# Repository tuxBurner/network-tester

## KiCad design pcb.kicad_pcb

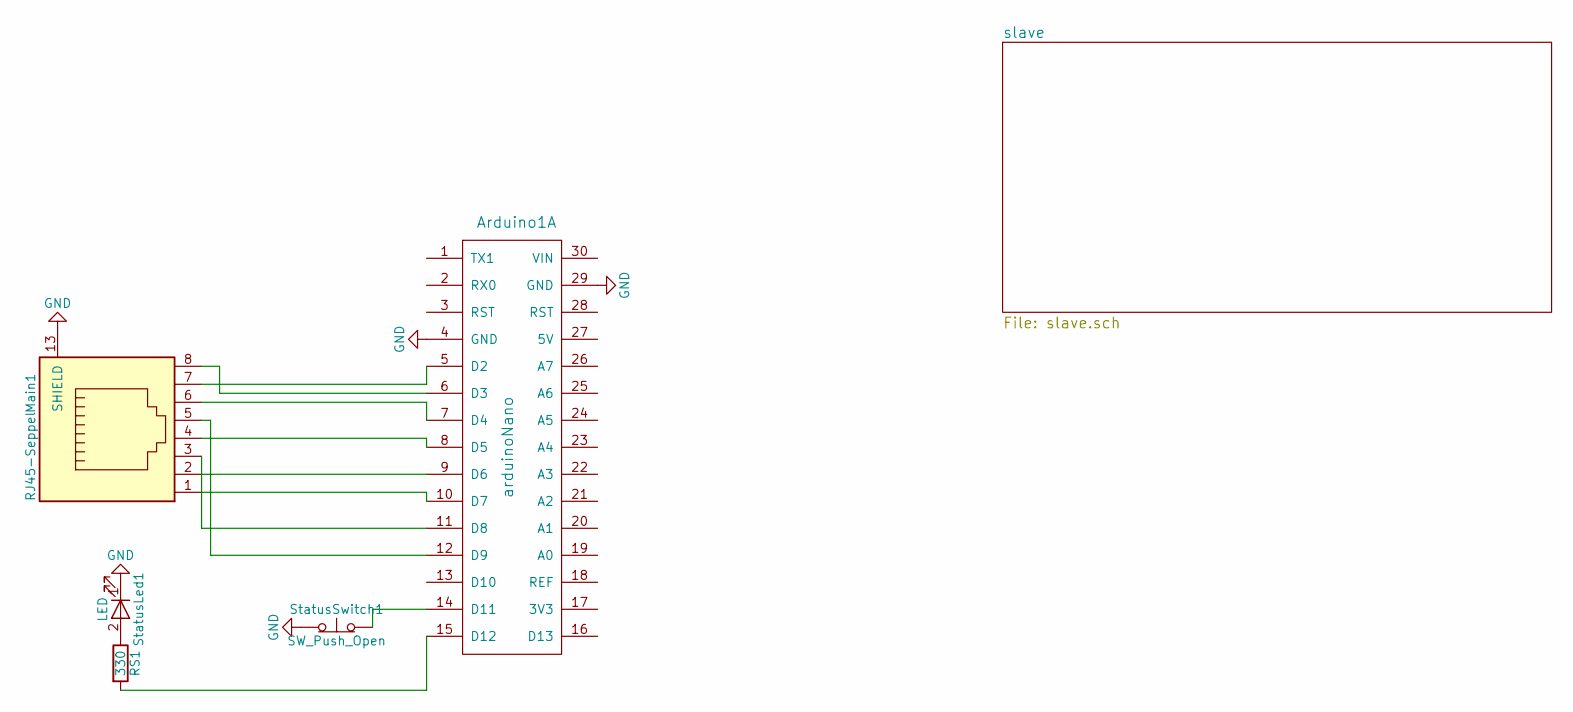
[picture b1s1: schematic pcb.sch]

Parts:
Arduino1: arduinoNano; Arduino_Nano
Main1: RJ45-Seppel; rj45-seppel-small
RS1: 330; R_Axial_DIN0207_L6.3mm_D2.5mm_P10.16mm_Horizontal
StatusLed1: LED; LED_D4.0mm
StatusSwitch1: SW_Push_Open; Pin_Header_Straight_1x02_Pitch2.54mm

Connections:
GND: Arduino1.4 (GND), Arduino1.29 (GND), Main1.13 (SHIELD), StatusLed1.1 (K), StatusSwitch1.1 (A)
unnamed: Arduino1.5 (D2), Main1.7
unnamed: Arduino1.6 (D3), Main1.8
unnamed: Arduino1.7 (D4), Main1.6
unnamed: Arduino1.8 (D5), Main1.4
unnamed: Arduino1.9 (D6), Main1.2
unnamed: Arduino1.10 (D7), Main1.1
unnamed: Arduino1.11 (D8), Main1.3
unnamed: Arduino1.12 (D9), Main1.5
unnamed: Arduino1.14 (D11), StatusSwitch1.2 (B)
unnamed: Arduino1.15 (D12), RS1.2
unnamed: RS1.1, StatusLed1.2 (A)

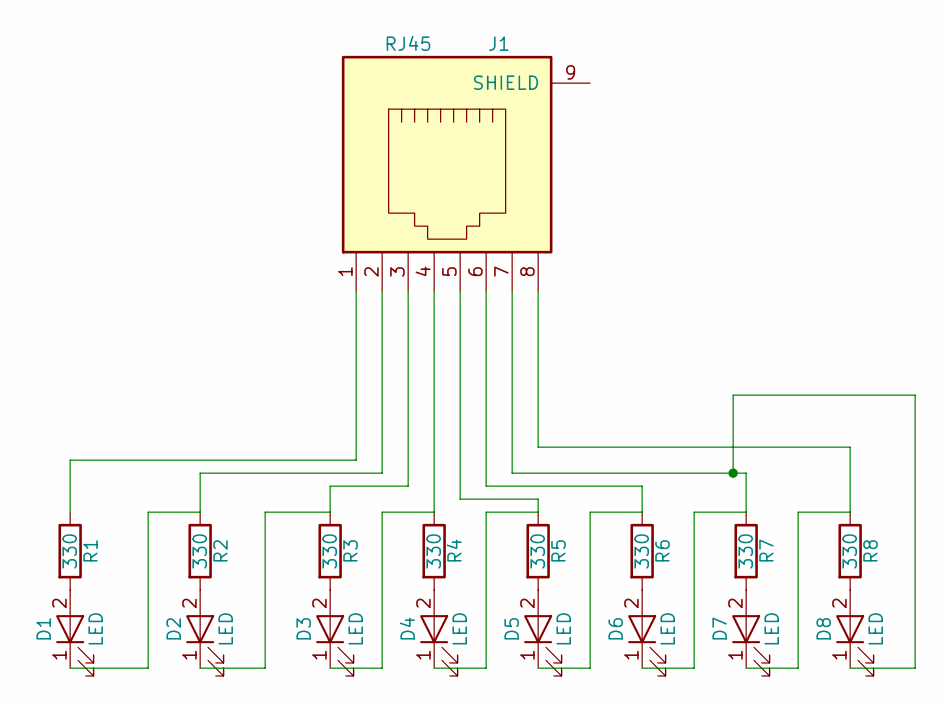
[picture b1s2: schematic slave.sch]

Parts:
D1, D2, D3, D4, D5, D6, D7, D8: LED; LED_D4.0mm
J1: RJ45; rj45-seppel-small
R1, R2, R3, R4, R5, R6, R7, R8: 330; R_Axial_DIN0207_L6.3mm_D2.5mm_P10.16mm_Horizontal

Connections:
unnamed: D1.1 (K), J1.2, R2.1
unnamed: D1.2 (A), R1.2
unnamed: D2.1 (K), J1.3, R3.1
unnamed: D2.2 (A), R2.2
unnamed: D3.1 (K), J1.4, R4.1
unnamed: D3.2 (A), R3.2
unnamed: D4.1 (K), J1.5, R5.1
unnamed: D4.2 (A), R4.2
unnamed: D5.1 (K), J1.6, R6.1
unnamed: D5.2 (A), R5.2
unnamed: D6.1 (K), D8.1 (K), J1.7, R7.1
unnamed: D6.2 (A), R6.2
unnamed: D7.1 (K), J1.8, R8.1
unnamed: D7.2 (A), R7.2
unnamed: D8.2 (A), R8.2
unnamed: J1.1, R1.1

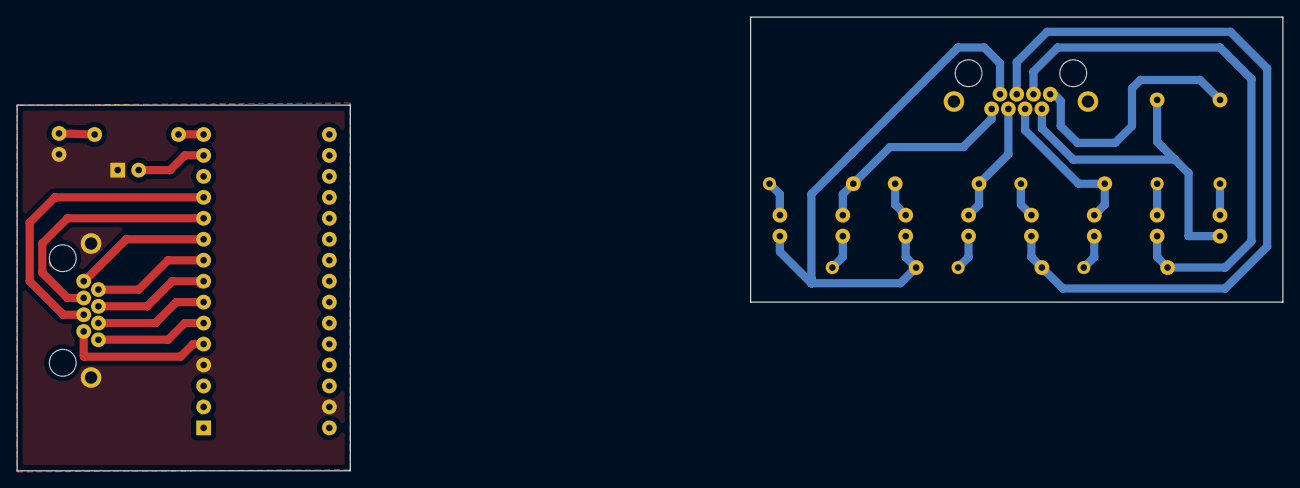
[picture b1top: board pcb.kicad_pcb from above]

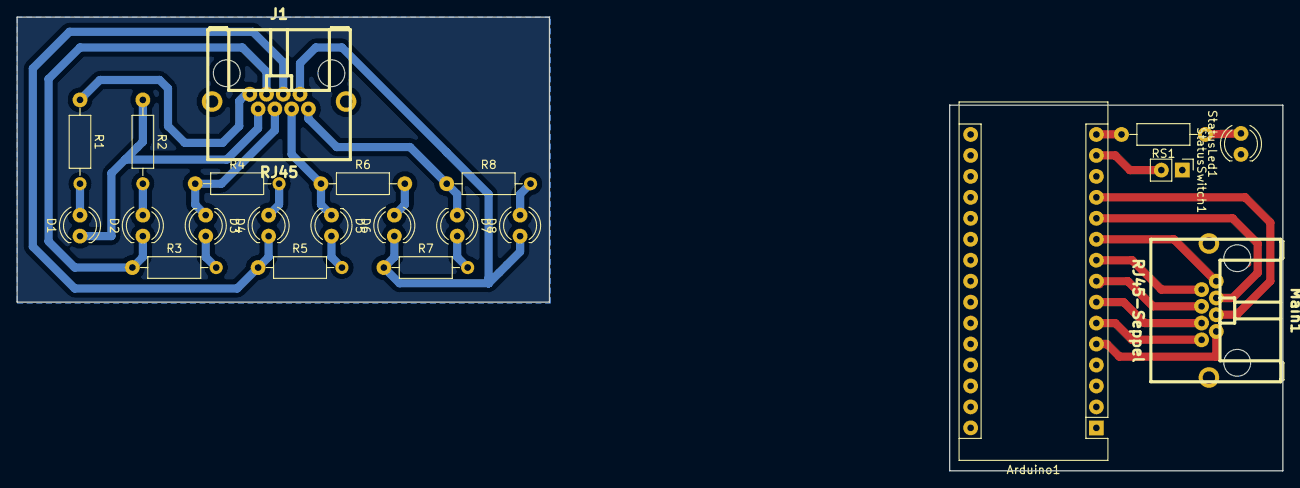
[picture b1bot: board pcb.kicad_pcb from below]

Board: 2 copper layers, 153.4 x 55.0 mm, 22 parts (22 on the bottom side), 28 nets.
